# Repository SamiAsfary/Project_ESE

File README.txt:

Project_ESE
├Electronics
│ ├System Diagram
│ │ └src
│ └PCB
├Programms
│ └STM32_Project
├Mechanics
│ ├Parts
│ └Robots
└Datasheets

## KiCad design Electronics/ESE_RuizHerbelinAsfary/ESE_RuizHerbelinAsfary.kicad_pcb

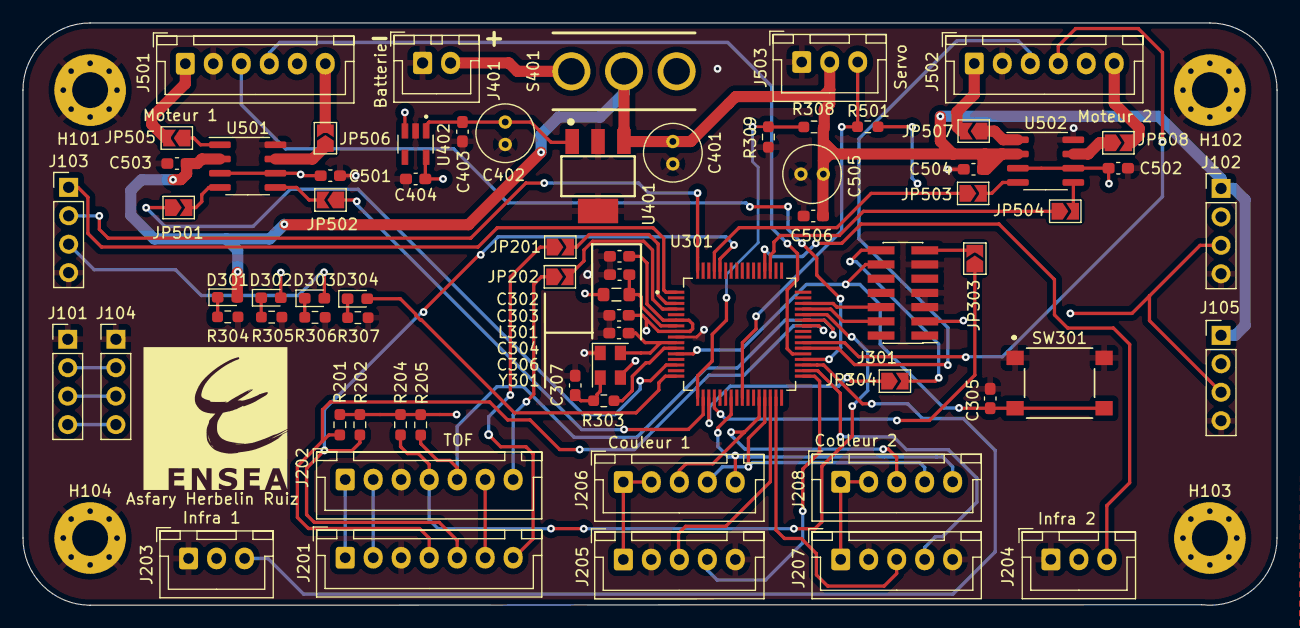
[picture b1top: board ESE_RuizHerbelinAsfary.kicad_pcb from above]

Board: 4 copper layers, 112.0 x 52.0 mm, 77 parts (1 on the bottom side), 64 nets.

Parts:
 : LOGO; logoEnsea
 #2: LOGO; bonk
C302: 4.7uF; C_0603_1608Metric_Pad1.08x0.95mm_HandSolder
C303, C304, C305, C501, C502, C506: 100nF; C_0603_1608Metric_Pad1.08x0.95mm_HandSolder
C306, C307: 10pF; C_0603_1608Metric_Pad1.08x0.95mm_HandSolder
C401: 10uF; C_Radial_D5.0mm_H5.0mm_P2.00mm
C402: 22uF; C_Radial_D5.0mm_H5.0mm_P2.00mm
C403, C404: 1uF; C_0603_1608Metric_Pad1.08x0.95mm_HandSolder
C503, C504: 10uF; C_0603_1608Metric_Pad1.08x0.95mm_HandSolder
C505: 1uF; C_Radial_D5.0mm_H5.0mm_P2.00mm
D301: Blue; LED_0603_1608Metric_Pad1.05x0.95mm_HandSolder
D302: Red; LED_0603_1608Metric_Pad1.05x0.95mm_HandSolder
D303: Yellow; LED_0603_1608Metric_Pad1.05x0.95mm_HandSolder
D304: Green; LED_0603_1608Metric_Pad1.05x0.95mm_HandSolder
H101, H102, H103, H104: MountingHole_Pad; MountingHole_3.2mm_M3_Pad_Via
J101, J104: I2C1; PinHeader_1x04_P2.54mm_Vertical
J102, J105: MTRX_test; PinHeader_1x04_P2.54mm_Vertical
J103: UART3; PinHeader_1x04_P2.54mm_Vertical
J201, J202: Conn_01x07_Female; JST_XH_B7B-XH-A_1x07_P2.50mm_Vertical
J203, J204, J503: Conn_01x03_Female; JST_XH_B3B-XH-A_1x03_P2.50mm_Vertical
J205, J206, J207, J208: Conn_01x05_Female; JST_XH_B5B-XH-A_1x05_P2.50mm_Vertical
J301: Conn_02x07_Odd_Even; PinHeader_2x07_P1.27mm_Vertical_SMD
J401: Conn_01x02_Female; JST_XH_B2B-XH-A_1x02_P2.50mm_Vertical
J501, J502: Conn_01x06_Female; JST_XH_B6B-XH-A_1x06_P2.50mm_Vertical
JP201, JP202, JP303, JP304, JP501, JP502, JP503, JP504, JP505, JP506, JP507, JP508: SolderJumper_2_Open; SolderJumper-2_P1.3mm_Open_TrianglePad1.0x1.5mm
L301: 600R@100MHz; L_0805_2012Metric_Pad1.05x1.20mm_HandSolder
R201, R202, R204, R205, R309: 2k; R_0603_1608Metric_Pad0.98x0.95mm_HandSolder
R303: 10R; R_0603_1608Metric_Pad0.98x0.95mm_HandSolder
R304: 2.4k; R_0603_1608Metric_Pad0.98x0.95mm_HandSolder
R305: 1.7k; R_0603_1608Metric_Pad0.98x0.95mm_HandSolder
R306, R307: 1.1k; R_0603_1608Metric_Pad0.98x0.95mm_HandSolder
R308: 6.5k; R_0603_1608Metric_Pad0.98x0.95mm_HandSolder
R501: 10k; R_0603_1608Metric_Pad0.98x0.95mm_HandSolder
S401: 1A11-NF5STSE-B
SW301: SW_MEC_5E; SWITCH_43SMTR92LFS
U301: STM32G070RBTx; QFP50P1200X1200X160-64N
U401: AZ1117_Reg5V; SOT230P700X180-4N
U402: MIC5317_Reg3V; SOT95P280X145-5N
U501, U502: ZXBM5210-S; SOIC-8_3.9x4.9mm_P1.27mm
Y301: 16MHz; Crystal_SMD_EuroQuartz_MT-4Pin_3.2x2.5mm

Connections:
+3.3V: C302.1, C304.1, C404.1, D303.2 (A), J102.3, J103.3, J105.3, J201.1, J201.2, J201.6, J202.1, J202.2, J202.6, J301.3, L301.2, R201.2, R202.1, R204.2, R205.1, R501.1, U301.6 (VBAT), U301.8 (VDD/VDDA), U402.5 (OUTPUT)
+5V: C402.1, C403.1, C501.1, C502.1, D302.2 (A), J101.2, J102.2, J104.2, J105.2, J203.2, J204.2, J205.1, J206.1, J206.2, J207.1, J208.1, J208.2, J501.5, J502.5, U401.3 (VOUT_OUTPUT), U402.1 (VIN), U402.3 (EN), U501.3 (VDD), U501.6 (VREF), U502.3 (VDD), U502.6 (VREF)
+BATT: C401.1, C503.1, C504.1, C505.2, C506.2, D301.2 (A), J102.1, J105.1, J503.2, R308.1, S401.2, U401.1 (VIN_INPUT), U501.2 (VM), U502.2 (VM)
/Actuator/EncoderA_Left: J501.3, U301.36 (PA8)
/Actuator/EncoderA_Right: J502.3, U301.38 (PC6)
/Actuator/EncoderB_Left: J501.4, U301.37 (PA9)
/Actuator/EncoderB_Right: J502.4, U301.39 (PC7)
/Actuator/FWD_LeftMotor_PWM: JP501.1 (A), U301.14 (PC1)
/Actuator/FWD_LeftMotor_PWM_JP: JP501.2 (B), U501.4 (FWD)
/Actuator/FWD_RightMotor_PWM: JP503.1 (A), U301.61 (PB7)
/Actuator/FWD_RightMotor_PWM_JP: JP503.2 (B), U502.4 (FWD)
/Actuator/MotorLFT_M: J501.1, JP505.2 (B)
/Actuator/MotorLFT_M_JP: JP505.1 (A), U501.1 (OUT1)
/Actuator/MotorLFT_P: J501.6, JP506.2 (B)
/Actuator/MotorLFT_P_JP: JP506.1 (A), U501.7 (OUT2)
/Actuator/MotorRGT_M: J502.1, JP507.2 (B)
/Actuator/MotorRGT_M_JP: JP507.1 (A), U502.1 (OUT1)
/Actuator/MotorRGT_P: J502.6, JP508.2 (B)
/Actuator/MotorRGT_P_JP: JP508.1 (A), U502.7 (OUT2)
/Actuator/REV_LeftMotor_PWM: JP502.1 (A), U301.18 (PA1)
/Actuator/REV_LeftMotor_PWM_JP: JP502.2 (B), U501.5 (REV)
/Actuator/REV_RightMotor_PWM: JP504.1 (A), U301.51 (PD1)
/Actuator/REV_RightMotor_PWM_JP: JP504.2 (B), U502.5 (REV)
/Actuator/UART_Servomoteur: J503.3, R501.2, U301.25 (PC4)
/Power_Supply/Alim: J401.2, S401.1
/STM32/LED1: J205.4, U301.33 (PB13)
/STM32/LED2: J207.4, U301.34 (PB14)
/STM32/NRST: C305.1, J301.12, SW301.3 (K), SW301.4 (A), U301.12 (NRST)
/STM32/OE1: J205.3, U301.30 (PB10)
/STM32/OE2: J207.3, U301.31 (PB11)
/STM32/OSCILLO_IN: C306.1, U301.10 (PF0-OSC_IN), Y301.4
/STM32/OSCILLO_OUT: R303.2, U301.11 (PF1-OSC_OUT)
/STM32/OSCILLO_OUT_R: C307.1, R303.1, Y301.2
/STM32/Out: J206.5, J208.5, U301.23 (PA6)
/STM32/POWER_STATUS_ADC: R308.2, R309.1, U301.17 (PA0)
/STM32/POWER_STATUS_LED: D304.2 (A), U301.16 (PC3)
/STM32/S2: J206.3, J208.3, U301.28 (PB1)
/STM32/S3: J206.4, J208.4, U301.29 (PB2)
/STM32/SCL1: J201.5, R202.2, U301.60 (PB6)
/STM32/SCL2: J202.5, R205.2, U301.43 (PA11[PA9])
/STM32/SDA1: J201.4, R201.1, U301.42 (PA10)
/STM32/SDA2: J202.4, R204.1, U301.44 (PA12[PA10])
/STM32/SWCLK: J301.6, U301.46 (PA14-BOOT0)
/STM32/SWDIO: J301.4, U301.45 (PA13)
/STM32/VCP_RX: JP303.1 (A), U301.20 (PA3)
/STM32/VCP_RX_JP: J301.13, JP303.2 (B)
/STM32/VCP_TX: JP304.1 (A), U301.19 (PA2)
/STM32/VCP_TX_JP: J301.14, JP304.2 (B)
/STM32/VREF: C303.1, L301.1, U301.7 (VREF+)
/STM32/Vout1: J203.3, U301.35 (PB15)
/STM32/Vout2: J204.3, U301.52 (PD2)
/Sensor/GPIO_TOF_1: JP201.2 (B), U301.3 (PC13)
/Sensor/GPIO_TOF_1_JP: J201.7, JP201.1 (A)
/Sensor/GPIO_TOF_2: JP202.2 (B), U301.4 (PC14-OSC32_IN)
/Sensor/GPIO_TOF_2_JP: J202.7, JP202.1 (A)
/UART_Rx: J103.1, U301.1 (PC11)
/UART_Tx: J103.2, U301.64 (PC10)
GND: C302.2, C303.2, C304.2, C305.2, C306.2, C307.2, C401.2, C402.2, C403.2, C404.2, C501.2, C502.2, C503.2, C504.2, C505.1, C506.1, H101.1, H102.1, H103.1, H104.1, J101.1, J102.4, J103.4, J104.1, J105.4, J201.3, J202.3, J203.1, J204.1, J205.2, J205.5, J207.2, J207.5, J301.5, J301.7, J301.11, J401.1, J501.2, J502.2, J503.1, R304.2, R305.2, R306.2, R307.2, R309.2, SW301.1, SW301.2, U301.9 (VSS/VSSA), U401.2 (GND), U401.4 (GND), U402.2 (GND), U501.8 (GND), U502.8 (GND), Y301.1, Y301.3
unnamed: D301.1 (K), R304.1
unnamed: D302.1 (K), R305.1
unnamed: D303.1 (K), R306.1
unnamed: D304.1 (K), R307.1
SCL: J101.4, J104.4
SDA: J101.3, J104.3

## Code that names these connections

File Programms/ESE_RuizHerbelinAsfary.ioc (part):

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Mcu.Name=STM32G070RBTx
Mcu.Package=LQFP64
Mcu.UserName=STM32G070RBTx
PA0.GPIOParameters=GPIO_Label
PA0.GPIO_Label=PWR_STS_ADC
PA0.Mode=IN0
PA0.Signal=ADC1_IN0
PA1.GPIOParameters=GPIO_Label
PA1.GPIO_Label=REV_LMTR_PWM
PA1.Mode=PWM Generation1 CH1 CH1N
PA1.Signal=TIM15_CH1N
PA10.GPIOParameters=GPIO_Label
PA10.GPIO_Label=TOF1_SDA
PA10.Mode=I2C
PA10.Signal=I2C1_SDA
PA11\ [PA9].GPIOParameters=GPIO_Label
PA11\ [PA9].GPIO_Label=TOF2_SCL
PA11\ [PA9].Mode=I2C
PA11\ [PA9].Signal=I2C2_SCL
PA12\ [PA10].GPIOParameters=GPIO_Label
PA12\ [PA10].GPIO_Label=TOF2_SDA
PA12\ [PA10].Mode=I2C
PA12\ [PA10].Signal=I2C2_SDA
PA13.Mode=Serial_Wire
PA13.Signal=SYS_SWDIO
PA14-BOOT0.Mode=Serial_Wire
PA14-BOOT0.Signal=SYS_SWCLK
PA2.GPIOParameters=GPIO_Label
PA2.GPIO_Label=VCP_TX
PA2.Mode=Asynchronous
PA2.Signal=USART2_TX
PA3.GPIOParameters=GPIO_Label
PA3.GPIO_Label=VCP_RX
PA3.Mode=Asynchronous
PA3.Signal=USART2_RX
PA6.GPIOParameters=GPIO_Label
PA6.GPIO_Label=COLOR_OUT
PA6.Signal=S_TIM16_CH1
PA8.GPIOParameters=GPIO_Label
PA8.GPIO_Label=ENC_L_A
PA8.Signal=S_TIM1_CH1
PA9.GPIOParameters=GPIO_Label
PA9.GPIO_Label=ENC_L_B
PA9.Signal=S_TIM1_CH2
PB1.GPIOParameters=GPIO_Label
PB1.GPIO_Label=COLOR_S2
PB1.Signal=GPIO_Output
PB10.GPIOParameters=GPIO_Label
PB10.GPIO_Label=COLOR_EN1
PB10.Signal=GPIO_Output
PB11.GPIOParameters=GPIO_Label
PB11.GPIO_Label=COLOR_EN2
PB11.Signal=GPIO_Output
PB13.GPIOParameters=GPIO_Label
PB13.GPIO_Label=COLOR_LED1
PB13.Signal=GPIO_Output
PB14.GPIOParameters=GPIO_Label
PB14.GPIO_Label=COLOR_LED2
PB14.Signal=GPIO_Output
PB15.GPIOParameters=GPIO_Label
PB15.GPIO_Label=INFRA1
PB15.Signal=GPXTI15
PB2.GPIOParameters=GPIO_Label
PB2.GPIO_Label=COLOR_S3
PB2.Signal=GPIO_Output
PB6.GPIOParameters=GPIO_Label
PB6.GPIO_Label=TOF1_SCL
PB6.Mode=I2C
PB6.Signal=I2C1_SCL
PB7.GPIOParameters=GPIO_Label
PB7.GPIO_Label=FWD_RMTR_PWM
PB7.Mode=PWM Generation1 CH1 CH1N
PB7.Signal=TIM17_CH1N
PC1.GPIOParameters=GPIO_Label
PC1.GPIO_Label=FWD_LMTR_PWM
PC1.Signal=S_TIM15_CH1
PC10.Mode=Asynchronous
PC10.Signal=USART3_TX
PC11.Mode=Asynchronous
PC11.Signal=USART3_RX
PC3.GPIOParameters=GPIO_Label
PC3.GPIO_Label=PWR_STS_LED
PC3.Signal=GPIO_Output
PC4.GPIOParameters=GPIO_Label
PC4.GPIO_Label=SERVO_UART
PC4.Mode=Half_duplex(single_wire_mode)
PC4.Signal=USART1_TX
PC6.GPIOParameters=GPIO_Label
PC6.GPIO_Label=ENC_R_A
PC6.Signal=S_TIM3_CH1
PC7.GPIOParameters=GPIO_Label
PC7.GPIO_Label=ENC_R_B
PC7.Signal=S_TIM3_CH2
PD1.GPIOParameters=GPIO_Label
PD1.GPIO_Label=REV_RMTR_PWM
PD1.Signal=S_TIM17_CH1
PD2.GPIOParameters=GPIO_Label
PD2.GPIO_Label=INFRA2
PD2.Signal=GPXTI2
PF0-OSC_IN\ (PF0).Signal=RCC_OSC_IN
PF1-OSC_OUT\ (PF1).Signal=RCC_OSC_OUT
RCC.HSE_VALUE=16000000
RCC.SYSCLKFreq_VALUE=64000000
RCC.SYSCLKSource=RCC_SYSCLKSOURCE_PLLCLK
board=custom

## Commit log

2022-09-30 Added STM32 and KiCAD project + changed Architecture Sensor
2022-09-30 Correctif last commit
2022-10-03 STM32 Symbol finished
2022-10-03 SWD connection finished
2022-10-03 Create text
2022-10-04 STM32 schematics done with comments and labels
2022-10-07 added test pin
2022-10-07 PCB finished
2022-10-11 added solderbridge before and after the driver
2022-10-13 added mounting hole
2022-12-01 Renamed pinout with label in the .ioc
